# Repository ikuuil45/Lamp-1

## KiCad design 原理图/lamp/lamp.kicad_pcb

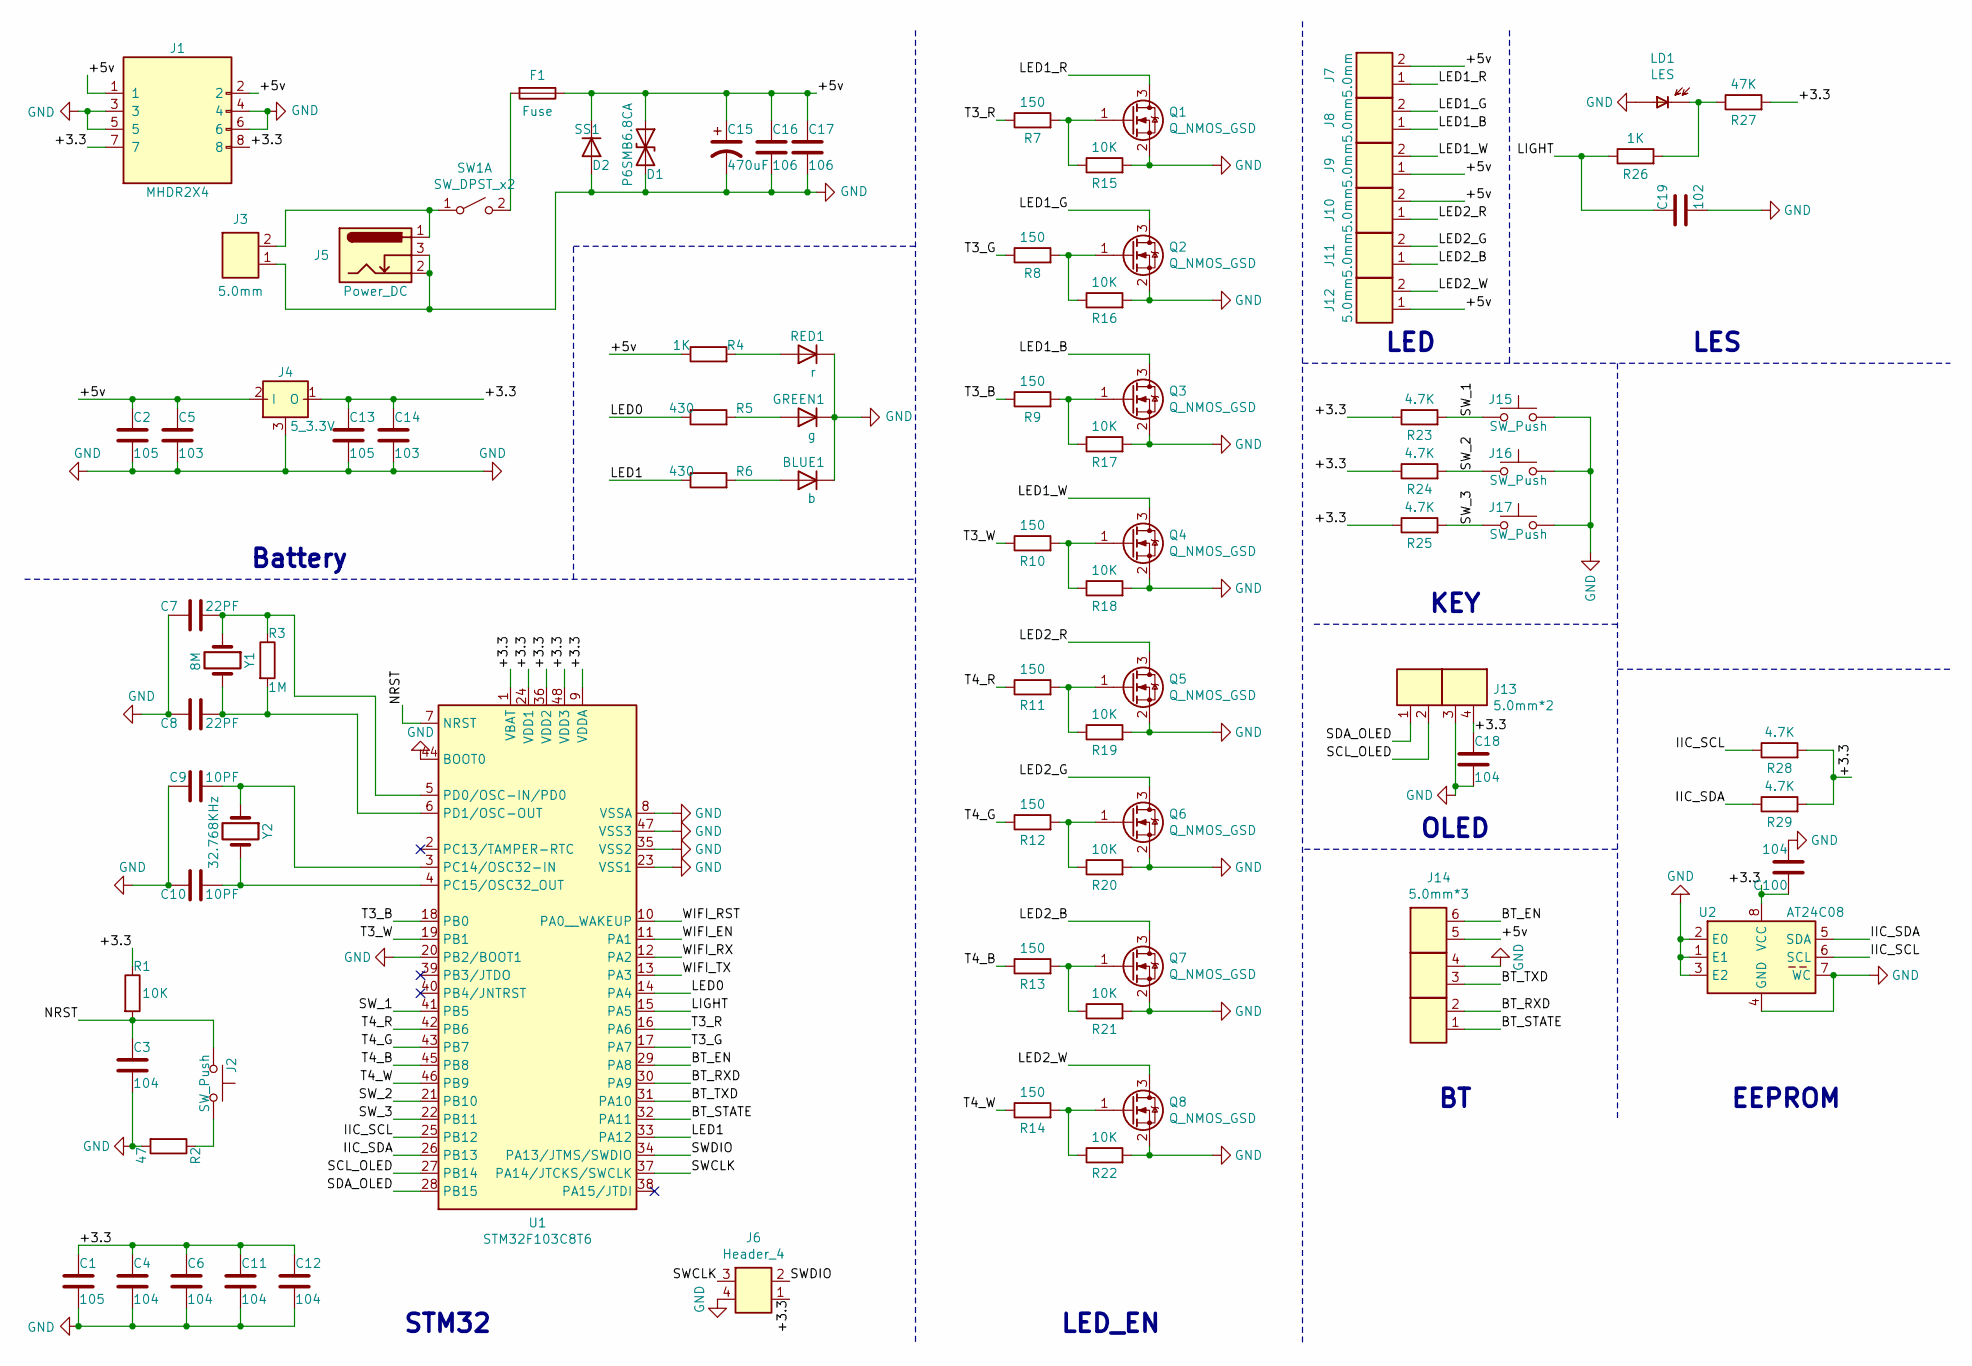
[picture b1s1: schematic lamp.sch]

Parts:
BLUE1: b; D_0603_1608Metric
C1, C2, C13: 105; C_0805_2012Metric
C3, C4, C6, C11, C12: 104; C_0805_2012Metric_Pad1.18x1.45mm_HandSolder
C5, C14: 103; C_0603_1608Metric
C7, C8: 22PF; C_0603_1608Metric
C9, C10: 10PF; C_0603_1608Metric
C15: 470uF; 470uF_Cap
C16, C17: 106; C_0805_2012Metric
C18, C100: 104; C_0805_2012Metric
C19: 102; C_0603_1608Metric_Pad1.08x0.95mm_HandSolder
D1: P6SMB6.8CA; D_SMB
F1: Fuse; D_1206_3216Metric_Pad1.42x1.75mm_HandSolder
GREEN1: g; D_0603_1608Metric
J1: MHDR2X4; PinHeader_2x04_P2.54mm_Vertical
J2, J15, J16, J17: SW_Push; SW_DIP_SPSTx01_Slide_6.7x4.1mm_W7.62mm_P2.54mm_LowProfile
J3, J7, J8, J9, J10, J11, J12: 5.0mm; TerminalBlock_Altech_AK300-2_P5.00mm
J4: 5_3.3V; SOT-223
J5: Power_DC; BarrelJack_Horizontal
J6: Header_4; PinHeader_2x02_P2.54mm_Vertical
J13: 5.0mm*2; PinHeader_1x04_P2.54mm_Vertical
J14: 5.0mm*3; PinHeader_1x06_P2.54mm_Vertical
LD1: LES; D_0805_2012Metric_Pad1.15x1.40mm_HandSolder
Q1, Q2, Q3, Q4, Q5, Q6, Q7, Q8: Q_NMOS_GSD; SOT23-3
R1, R15, R16, R17, R18, R19, R20, R21, R22: 10K; R_0805_2012Metric_Pad1.20x1.40mm_HandSolder
R2: 47; R_0805_2012Metric_Pad1.20x1.40mm_HandSolder
R3: 1M; R_0805_2012Metric_Pad1.20x1.40mm_HandSolder
R4, R26: 1K; R_0805_2012Metric_Pad1.20x1.40mm_HandSolder
R5, R6: 430; R_0805_2012Metric_Pad1.20x1.40mm_HandSolder
R7, R8, R9, R10, R11, R12, R13, R14: 150; R_0805_2012Metric_Pad1.20x1.40mm_HandSolder
R23, R24, R25, R28, R29: 4.7K; R_0805_2012Metric_Pad1.20x1.40mm_HandSolder
R27: 47K; R_0805_2012Metric_Pad1.20x1.40mm_HandSolder
RED1: r; D_0603_1608Metric
SS1: D2; D_SMA
SW1: SW_DPST_x2; Kan-90
U1: STM32F103C8T6; LQFP-48_7x7mm_P0.5mm
U2: AT24C08; DIP-8_AT24C08
Y1: 8M; Crystal_SMD_5032-2Pin_5.0x3.2mm_HandSoldering
Y2: 32.768KHz; Crystal_SMD_3215-2Pin_3.2x1.5mm

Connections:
/+3.3: C1.1, C4.1, C6.1, C11.1, C12.1, C13.1, C14.1, C18.1, C100.1, J1.7, J1.8, J4.1 (O), J6.1, J13.4, R1.1, R23.1, R24.1, R25.1, R27.2, R28.2, R29.2, U1.1 (VBAT), U1.9 (VDDA), U1.24 (VDD1), U1.36 (VDD2), U1.48 (VDD3), U2.8 (VCC)
/+5v: C2.1, C5.1, C15.1, C16.1, C17.1, D1.1 (A1), F1.1, J1.1, J1.2, J4.2 (I), J7.2, J9.1, J10.2, J12.1, J14.5, R4.1, SS1.2 (K)
/BT_EN: J14.6, U1.29 (PA8)
/BT_RXD: J14.2, U1.30 (PA9)
/BT_STATE: J14.1, U1.32 (PA11)
/BT_TXD: J14.3, U1.31 (PA10)
/IIC_SCL: R28.1, U1.25 (PB12), U2.6 (SCL)
/IIC_SDA: R29.1, U1.26 (PB13), U2.5 (SDA)
/LED0: R5.1, U1.14 (PA4)
/LED1: R6.1, U1.33 (PA12)
/LED1_B: J8.1, Q3.3 (D)
/LED1_G: J8.2, Q2.3 (D)
/LED1_R: J7.1, Q1.3 (D)
/LED1_W: J9.2, Q4.3 (D)
/LED2_B: J11.1, Q7.3 (D)
/LED2_G: J11.2, Q6.3 (D)
/LED2_R: J10.1, Q5.3 (D)
/LED2_W: J12.2, Q8.3 (D)
/LIGHT: C19.2, R26.1, U1.15 (PA5)
/NRST: C3.1, J2.1, R1.2, U1.7 (NRST)
/SCL_OLED: J13.2, U1.27 (PB14)
/SDA_OLED: J13.1, U1.28 (PB15)
/SWCLK: J6.3, U1.37 (PA14/JTCKS/SWCLK)
/SWDIO: J6.2, U1.34 (PA13/JTMS/SWDIO)
/SW_1: J15.1, R23.2, U1.41 (PB5)
/SW_2: J16.1, R24.2, U1.21 (PB10)
/SW_3: J17.1, R25.2, U1.22 (PB11)
/T3_B: R9.1, U1.18 (PB0)
/T3_G: R8.1, U1.17 (PA7)
/T3_R: R7.1, U1.16 (PA6)
/T3_W: R10.1, U1.19 (PB1)
/T4_B: R13.1, U1.45 (PB8)
/T4_G: R12.1, U1.43 (PB7)
/T4_R: R11.1, U1.42 (PB6)
/T4_W: R14.1, U1.46 (PB9)
/WIFI_EN: U1.11 (PA1)
/WIFI_RST: U1.10 (PA0__WAKEUP)
/WIFI_RX: U1.12 (PA2)
/WIFI_TX: U1.13 (PA3)
GND: BLUE1.2 (K), C1.2, C2.2, C3.2, C4.2, C5.2, C6.2, C7.2, C8.2, C9.2, C10.2, C11.2, C12.2, C13.2, C14.2, C15.2, C16.2, C17.2, C18.2, C19.1, C100.2, D1.2 (A2), GREEN1.2 (K), J1.3, J1.4, J1.5, J1.6, J3.1, J4.3, J5.2, J5.3, J6.4, J13.3, J14.4, J15.2, J16.2, J17.2, LD1.1 (A), Q1.2 (S), Q2.2 (S), Q3.2 (S), Q4.2 (S), Q5.2 (S), Q6.2 (S), Q7.2 (S), Q8.2 (S), R2.2, R15.2, R16.2, R17.2, R18.2, R19.2, R20.2, R21.2, R22.2, RED1.2 (K), SS1.1 (A), U1.8 (VSSA), U1.20 (PB2/BOOT1), U1.23 (VSS1), U1.35 (VSS2), U1.44 (BOOT0), U1.47 (VSS3), U2.1 (E1), U2.2 (E0), U2.3 (E2), U2.4 (GND), U2.7 (WC)
unnamed: BLUE1.1 (A), R6.2
unnamed: C7.1, R3.1, U1.5 (PD0/OSC-IN/PD0), Y1.1
unnamed: C8.1, R3.2, U1.6 (PD1/OSC-OUT), Y1.2
unnamed: C9.1, U1.3 (PC14/OSC32-IN), Y2.1
unnamed: C10.1, U1.4 (PC15/OSC32_OUT), Y2.2
unnamed: F1.2, SW1.2 (B)
unnamed: GREEN1.1 (A), R5.2
unnamed: J2.2, R2.1
unnamed: J3.2, J5.1, SW1.1 (A)
unnamed: LD1.2 (K), R26.2, R27.1
unnamed: Q1.1 (G), R7.2, R15.1
unnamed: Q2.1 (G), R8.2, R16.1
unnamed: Q3.1 (G), R9.2, R17.1
unnamed: Q4.1 (G), R10.2, R18.1
unnamed: Q5.1 (G), R11.2, R19.1
unnamed: Q6.1 (G), R12.2, R20.1
unnamed: Q7.1 (G), R13.2, R21.1
unnamed: Q8.1 (G), R14.2, R22.1
unnamed: R4.2, RED1.1 (A)

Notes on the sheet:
Battery
STM32
LED_EN
LED
KEY
OLED
EEPROM
LES

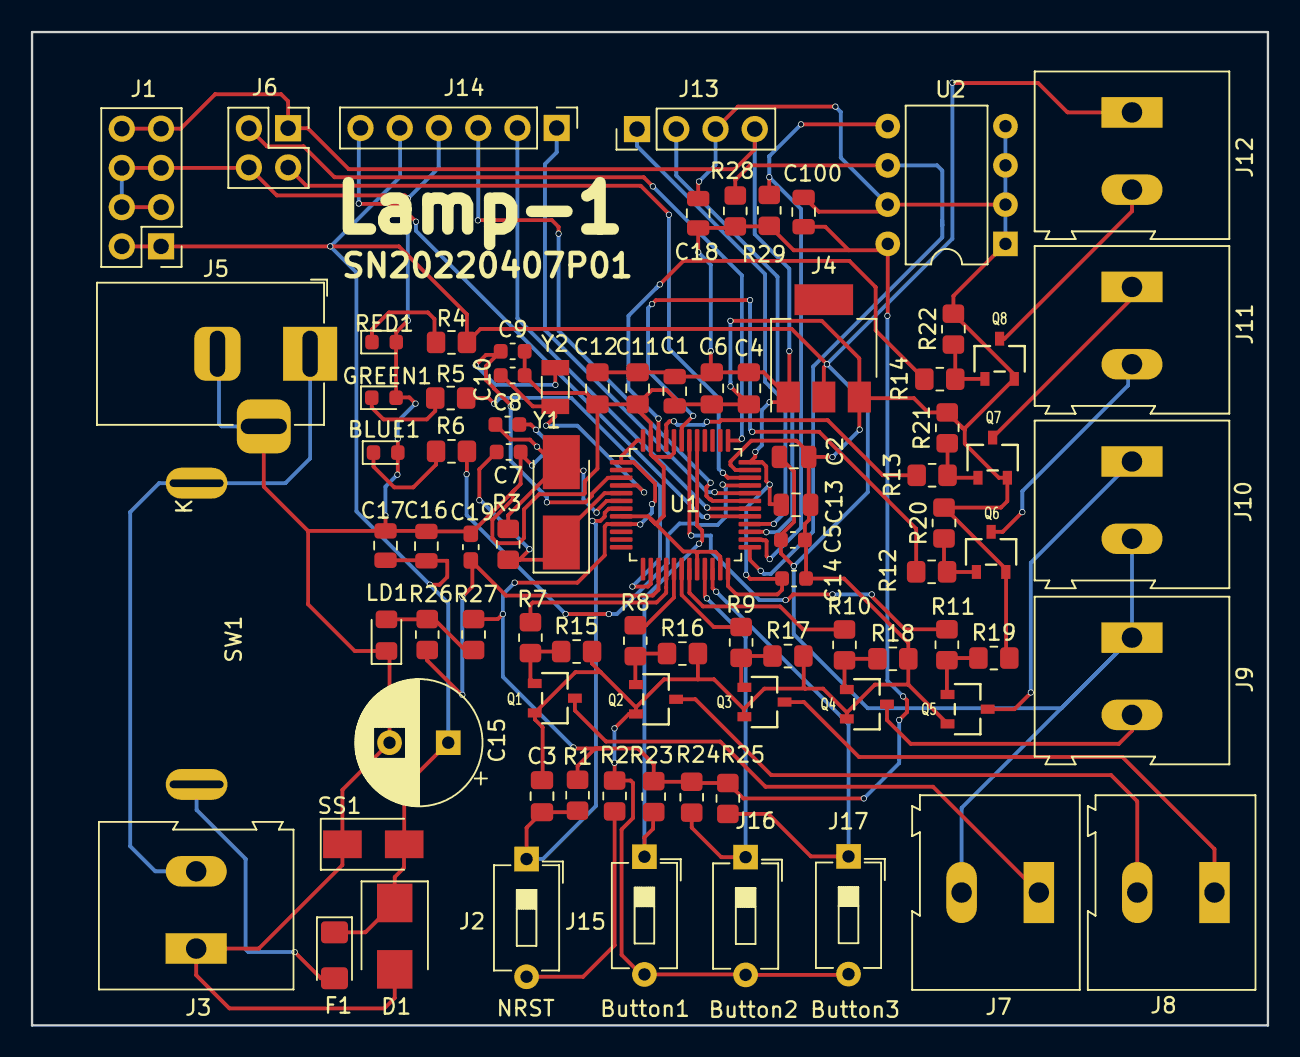
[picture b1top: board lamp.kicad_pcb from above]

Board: 2 copper layers, 80.0 x 64.3 mm, 86 parts (0 on the bottom side), 55 nets.

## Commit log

2022-06-29 提交文件
